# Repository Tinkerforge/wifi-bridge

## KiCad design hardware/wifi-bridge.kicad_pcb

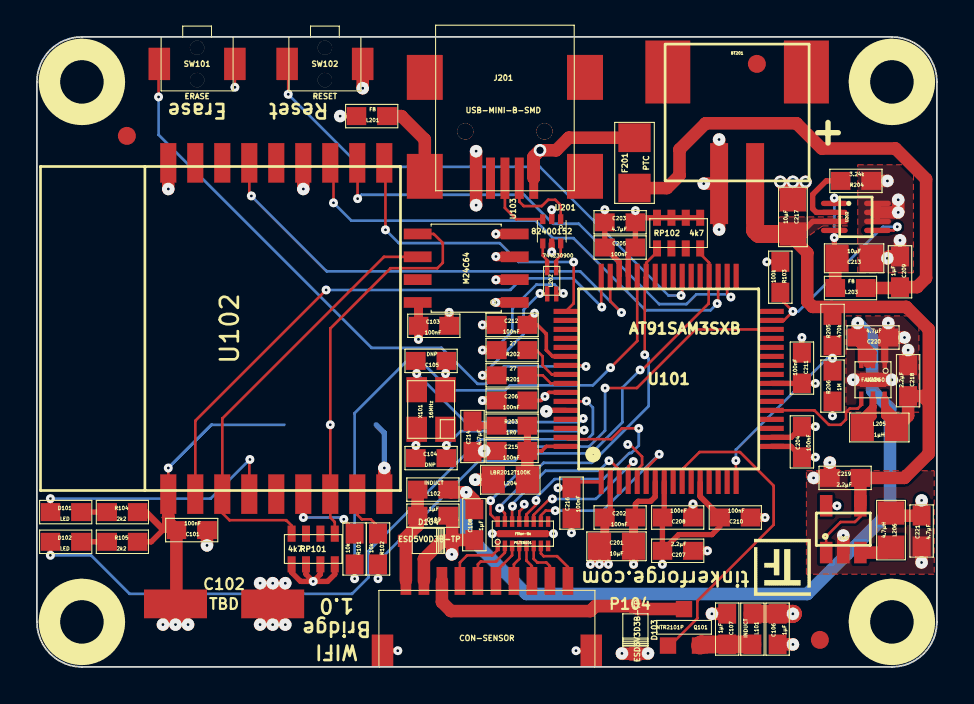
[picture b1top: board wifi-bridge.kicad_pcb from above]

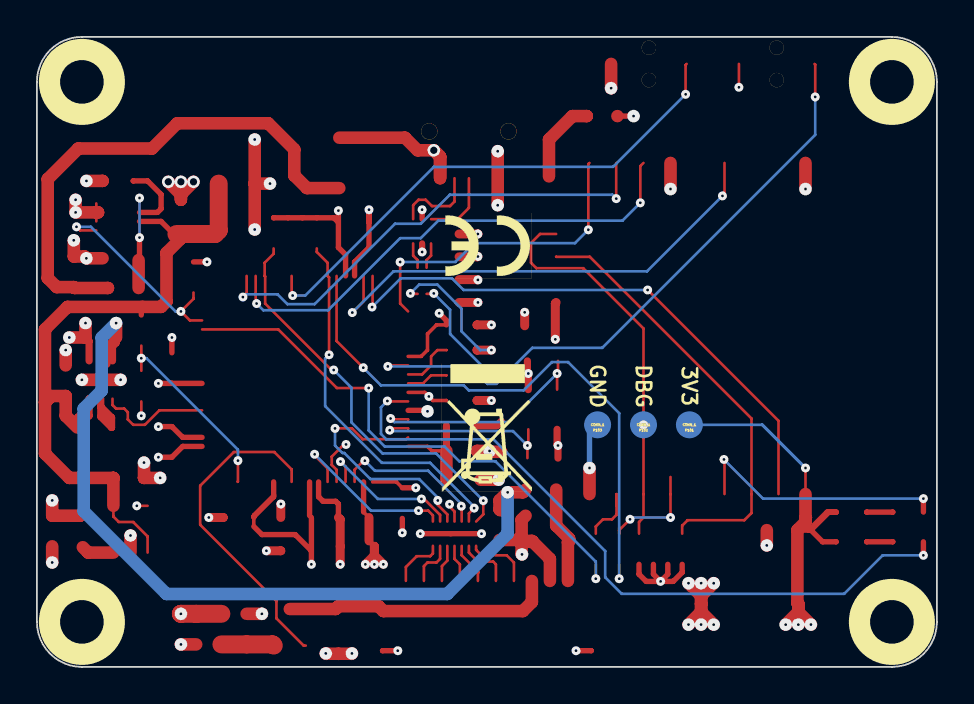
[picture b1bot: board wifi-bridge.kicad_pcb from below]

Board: 4 copper layers, 50.0 x 35.0 mm, 83 parts (5 on the bottom side), 62 nets.

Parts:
BT201: BATTERY; JST-PH-SM4-2
C101, C103, C202, C204, C205, C206, C208, C210, C211, C212, C215, C216: 100nF; 0603E
C102: TBD; ELKO_63
C104, C105: DNP; 0603E
C106, C107, C108, C109, C209: 1µF; 0603E
C201, C213, C217: 10µF; 0805E
C203, C214, C220, C221: 4.7µF; 0603E
C207, C218, C219: 2.2µF; 0603E
D101, D102: LED; 0603E
D103: ESD3V3D3B-TP; SOD-323
D104: ESD5V0D3B-TP; SOD-323
F201: PTC; 1206E
FILTER101: Filter-8x; DFN16-33x135
Fiducial_Mark: VAL**; Fiducial_Mark
Fiducial_Mark#2, Fiducial_Mark#3: VAL**; Fiducial_Mark
J201: USB-MINI-B-SMD
L101, L102: INDUCT; 0603E
L201, L203: FB; 0603E
L202: 744230900; WE-CNSW-0603
L204: LBR2012T100K; 0805E
L205: 1µH; 0805E
L206: 4.7µH; 0805E
P101, P102, P103: CONN_1; TSTPT
P104: CON-SENSOR
Q101: NTR2101P; SOT23GDS
R101, R102: 10k; 0603E
R103: 100k; 0603E
R104, R105: 2k2; 0603E
R201, R202: 27; 0603E
R203: 1R0; 0603E
R204: 3.24k; 0603E
R205: 470k; 0603E
R206: 1M; 0603E
RP101, RP102: 4k7; 0603X4
SW101: ERASE; TACT-SWITCH
SW102: RESET; TACT-SWITCH
U101: AT91SAM3SXB; LQFP64
U102: ESP8266_WROOM02
U103: M24C64; SOIC8
U104, U105, U106, U107: DRILL; DRILL_NP
U201: 82400152; SOT563-SPEC
U202: AAT3681A; SC70JW-8
U203: PAM2301; TSOT-25
U204: FAN4860; UMLP_22
VAL: WEEE_7mm_back
VAL#2: CE_5mm
X101: 16MHz; CRYSTAL_3225

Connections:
3V3: C101.1, C102.1, C103.2, C106.1, C201.1, C202.1, C203.1, C204.1, C205.1, C206.1, C216.1, C221.1, L101.2, L206.2, P101.1, R103.2, R104.1, R105.1, RP101.1, RP101.2, RP101.3, RP101.4, RP102.1, RP102.2, RP102.3, RP102.4, SW101.2, U101.1, U101.7, U101.18, U101.45, U101.58, U102.1, U103.1, U103.8, U203.5
5VEN: U101.21, U204.4
+5V: C108.1, C220.1, L102.2, U204.2, U204.3
B-ADR: FILTER101.14, U101.3
B-IO1: FILTER101.13, U101.5
B-IO2: FILTER101.12, U101.63
B-IO3: FILTER101.11, U101.4
B-IO4: FILTER101.10, U101.6
B-SCL: FILTER101.16, RP102.8, U101.36
B-SDA: FILTER101.15, RP102.5, U101.43
CHST: R103.1, U101.31, U202.5
D+: R201.2, U101.57
D-: R202.2, U101.56
GND: BT201.2, C101.2, C102.2, C103.1, C104.2, C105.2, C106.2, C107.2, C108.2, C109.2, C201.2, C202.2, C203.2, C204.2, C205.2, C206.2, C207.2, C208.2, C209.2, C210.2, C211.2, C212.2, C213.2, C214.2, C215.2, C216.2, C217.2, C218.2, C219.2, C220.2, C221.2, D103.2, D104.2, FILTER101.EXP, J201.5, L201.1, P103.1, P104.2, P104.EP, R204.2, R206.2, SW102.2, U101.2, U101.17, U101.46, U101.60, U102.9, U102.13, U102.18, U103.2, U103.3, U103.4, U201.2, U202.6, U202.7, U202.8, U203.2, U204.1, U204.EP, X101.3
LED: D102.2, U101.59
unnamed: C104.1, U101.62, X101.1
unnamed: C105.1, U101.61, X101.2
unnamed: C107.1, L101.1, Q101.S
unnamed: C109.1, D104.1, L102.1, P104.1
unnamed: C207.1, C208.1, C210.1, C211.1, C212.1, L204.1, U101.8, U101.12, U101.24, U101.54
unnamed: C209.1, F201.2, L203.2
unnamed: C213.1, L203.1, U202.1, U202.4
unnamed: C214.1, R203.2
unnamed: C215.1, L204.2, R203.1, U101.64
unnamed: D101.1, R104.2
unnamed: D101.2, U102.4
unnamed: D102.1, R105.2
unnamed: D103.1, P104.3, Q101.D
unnamed: F201.1, J201.1, U201.5
unnamed: FILTER101.1, P104.4
unnamed: FILTER101.2, P104.5
unnamed: FILTER101.3, P104.6
unnamed: FILTER101.4, P104.7
unnamed: FILTER101.5, P104.8
unnamed: FILTER101.6, P104.9
unnamed: FILTER101.7, P104.10
unnamed: J201.2, U201.1
unnamed: J201.3, U201.3
unnamed: J201.6, L201.2
unnamed: L202.1, R201.1
unnamed: L202.2, U201.4
unnamed: L202.3, U201.6
unnamed: L202.4, R202.1
unnamed: L205.2, U204.5
unnamed: L206.1, U203.3
unnamed: R101.2, U102.6
unnamed: R102.2, U102.8
unnamed: R204.1, U202.2
unnamed: SW101.1, U101.55
unnamed: SW102.1, U101.39
SW-3V3: Q101.G, U101.10
VBAT: R205.2, R206.1, U101.16
VCC: BT201.1, C217.1, C218.1, C219.1, L205.1, R205.1, U202.3, U203.1, U203.4, U204.6
W-EN: U101.48, U102.2
W-GP: U101.49, U102.10
W-IO0: R102.1, U101.30
W-IO15: R101.1, U101.44
W-RST: U101.47, U102.15
W-RXD: U101.34, U102.11
W-SCL: RP101.8, U102.3, U103.6
W-SDA: P102.1, RP101.5, U102.7, U103.5
W-TXD: U101.35, U102.12

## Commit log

2015-09-09 initial checkin
2015-09-09 first schematic parts added, many connections missing, prepare first placement
2015-09-09 new placement idea
2015-09-09 missing commit, things changed
2015-09-10 new placement mockup
2015-09-11 placement complete
2015-09-11 fixed schematic, add tvs diodes, placement changed, clear for routing
2015-09-11 fully routed
2015-09-11 add planes, add logos etc.
2015-09-11 round corners
2015-09-11 version for prototype order
2015-09-22 add hints to the schematic, add demo code
2015-09-28 bugfix erase button was connected to GND
2015-09-28 fix pcb (erase button to vcc)
2015-09-28 fix powering problem when battery is not connected
2015-09-28 add lipo connector hint
2015-09-28 charging detect implemented
2016-02-09 Add WIP marker
2021-10-25 Update KiCad link
    https://www.kicad.org/blog/2021/10/Avoid-links-to-former-kicad-domain/
